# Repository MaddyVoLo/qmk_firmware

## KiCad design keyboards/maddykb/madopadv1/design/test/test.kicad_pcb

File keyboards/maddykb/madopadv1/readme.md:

# madopadv1

*A short description of the keyboard/project*

* Keyboard Maintainer: [Madeline Panak](https://github.com/VoLodiaa1)
* Hardware Supported: *The PCBs, controllers supported*
* Hardware Availability: *Links to where you can find this hardware*

Make example for this keyboard (after setting up your build environment):

    make madopadv1:default

Flashing example for this keyboard:

    make madopadv1:default:flash

See the [build environment setup](https://docs.qmk.fm/#/getting_started_build_tools) and the [make instructions](https://docs.qmk.fm/#/getting_started_make_guide) for more information. Brand new to QMK? Start with our [Complete Newbs Guide](https://docs.qmk.fm/#/newbs).

## Bootloader

Enter the bootloader in 3 ways:

* **Bootmagic reset**: Hold down the key at (0,0) in the matrix (usually the top left key or Escape) and plug in the keyboard
* **Physical reset button**: Briefly press the button on the back of the PCB - some may have pads you must short instead
* **Keycode in layout**: Press the key mapped to `QK_BOOT` if it is available

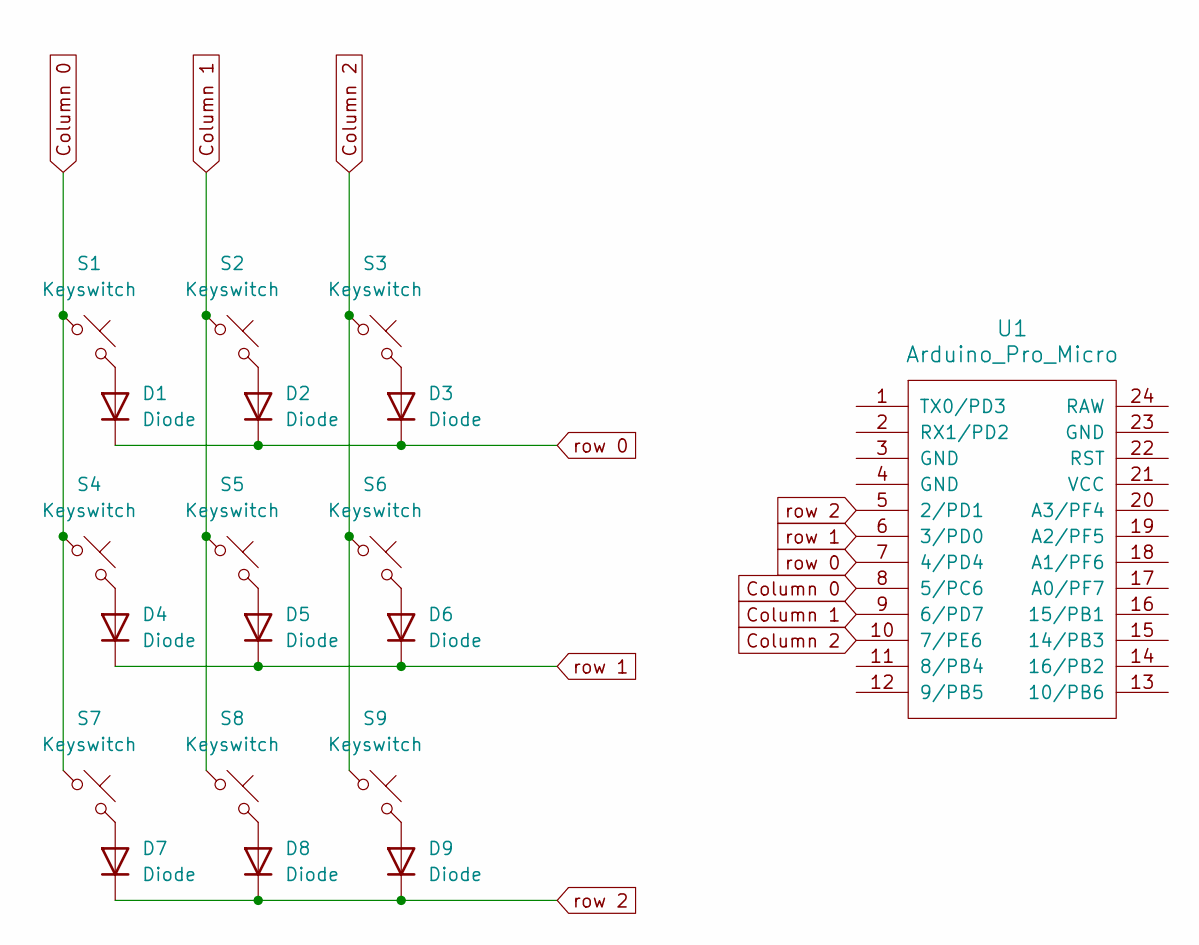
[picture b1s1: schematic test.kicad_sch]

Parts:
D1, D2, D3, D4, D5, D6, D7, D8, D9: Diode; D_SOD-123
S1, S2, S3, S4, S5, S6, S7, S8, S9: Keyswitch; MX_PCB_1.00u
U1: Arduino_Pro_Micro

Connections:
Column 0: S1.1, S4.1, S7.1, U1.8 (5/PC6)
Column 1: S2.1, S5.1, S8.1, U1.9 (6/PD7)
Column 2: S3.1, S6.1, S9.1, U1.10 (7/PE6)
unnamed: D1.2 (A), S1.2
unnamed: D2.2 (A), S2.2
unnamed: D3.2 (A), S3.2
unnamed: D4.2 (A), S4.2
unnamed: D5.2 (A), S5.2
unnamed: D6.2 (A), S6.2
unnamed: D7.2 (A), S7.2
unnamed: D8.2 (A), S8.2
unnamed: D9.2 (A), S9.2
row 0: D1.1 (K), D2.1 (K), D3.1 (K), U1.7 (4/PD4)
row 1: D4.1 (K), D5.1 (K), D6.1 (K), U1.6 (3/PD0)
row 2: D7.1 (K), D8.1 (K), D9.1 (K), U1.5 (2/PD1)

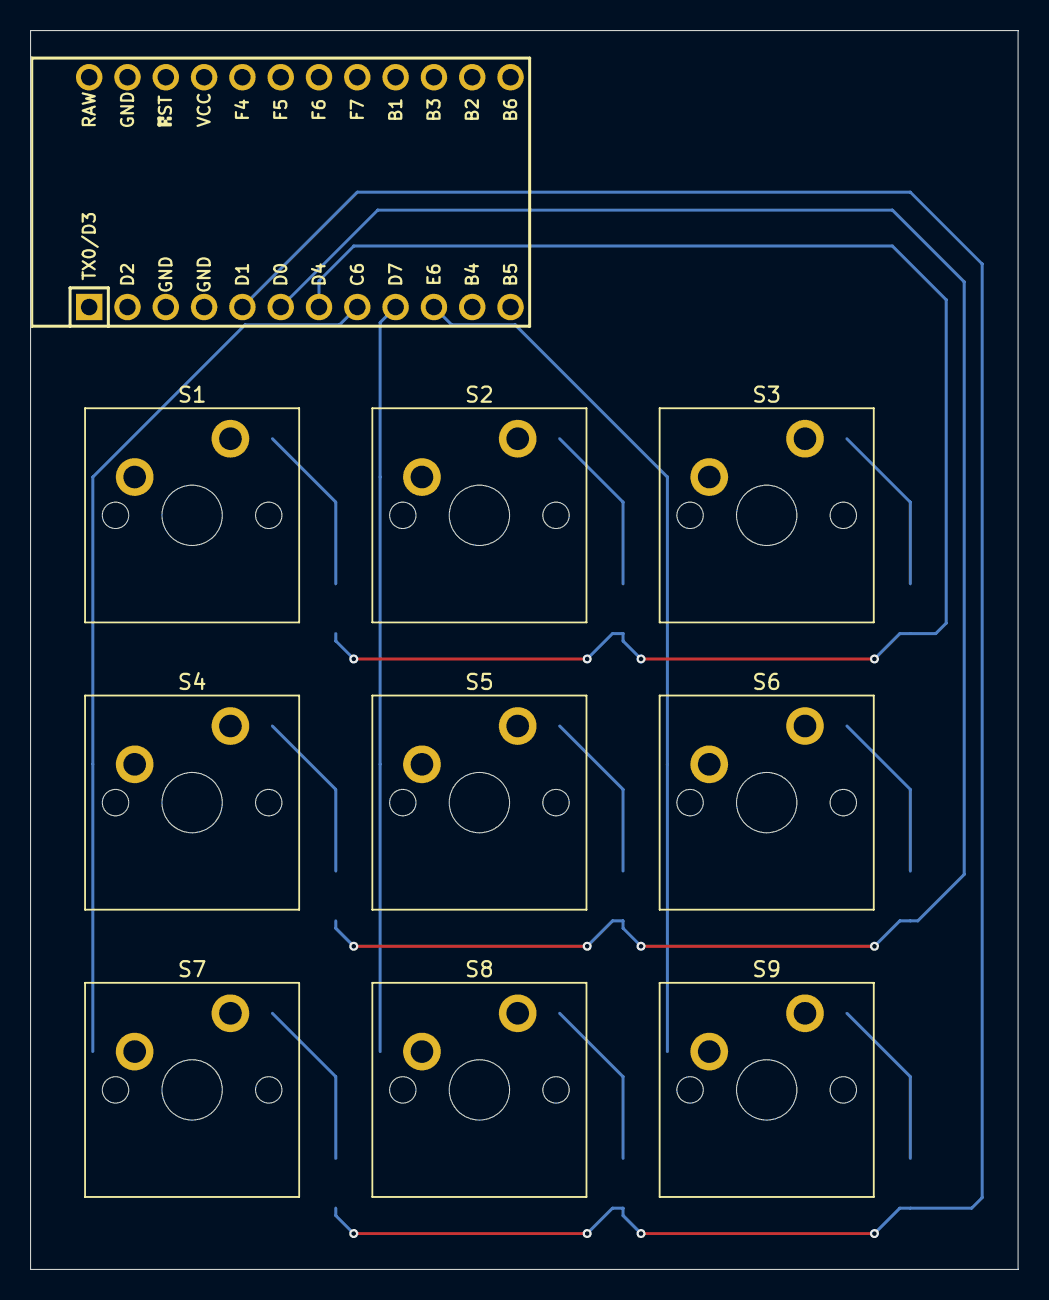
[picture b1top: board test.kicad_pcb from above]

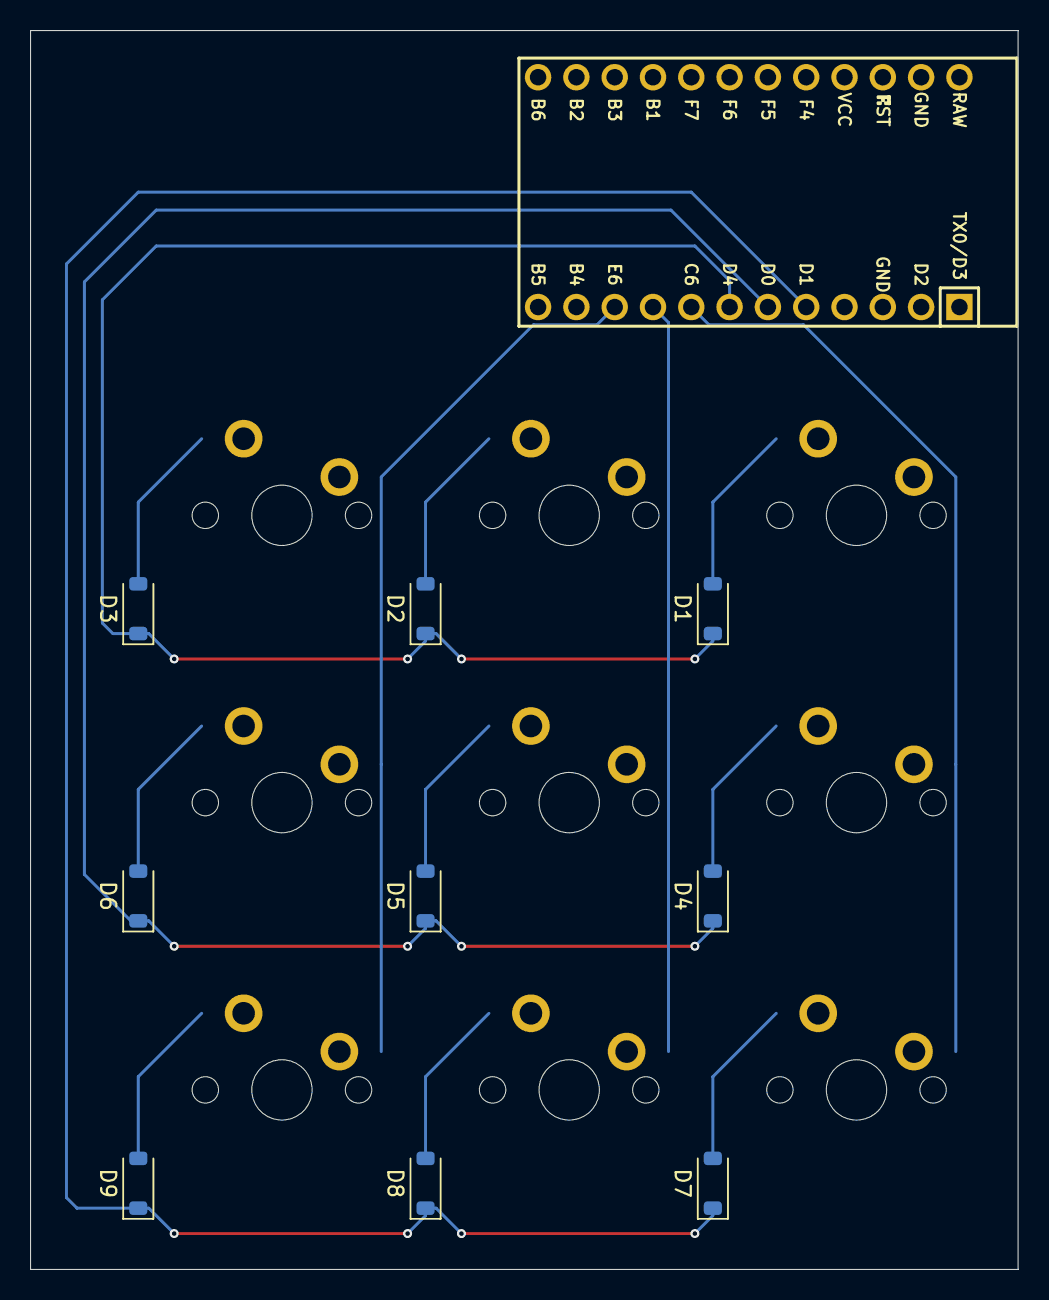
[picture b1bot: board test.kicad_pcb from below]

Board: 2 copper layers, 65.5 x 82.2 mm, 19 parts (9 on the bottom side), 15 nets.

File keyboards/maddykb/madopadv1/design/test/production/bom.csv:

Designator,Footprint,Quantity,Value,LCSC Part #
"D1, D2, D3, D4, D5, D6, D7, D8, D9",D_SOD-123,9,Diode,
"S1, S2, S3, S4, S5, S6, S7, S8, S9",Hotswap_MX_Plated_1.00u,9,Keyswitch,
U1,Arduino_Pro_Micro,1,Arduino_Pro_Micro,

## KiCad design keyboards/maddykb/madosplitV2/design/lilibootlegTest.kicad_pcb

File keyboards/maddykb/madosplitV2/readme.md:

# madosplit

*A short description of the keyboard/project*

* Keyboard Maintainer: [Madeline Panak](https://github.com/VoLodiaa1)
* Hardware Supported: *The PCBs, controllers supported*
* Hardware Availability: *Links to where you can find this hardware*

Make example for this keyboard (after setting up your build environment):

    make madosplit:default

Flashing example for this keyboard:

    make madosplit:default:flash

See the [build environment setup](https://docs.qmk.fm/#/getting_started_build_tools) and the [make instructions](https://docs.qmk.fm/#/getting_started_make_guide) for more information. Brand new to QMK? Start with our [Complete Newbs Guide](https://docs.qmk.fm/#/newbs).

## Bootloader

Enter the bootloader in 3 ways:

* **Bootmagic reset**: Hold down the key at (0,0) in the matrix (usually the top left key or Escape) and plug in the keyboard
* **Physical reset button**: Briefly press the button on the back of the PCB - some may have pads you must short instead
* **Keycode in layout**: Press the key mapped to `QK_BOOT` if it is available

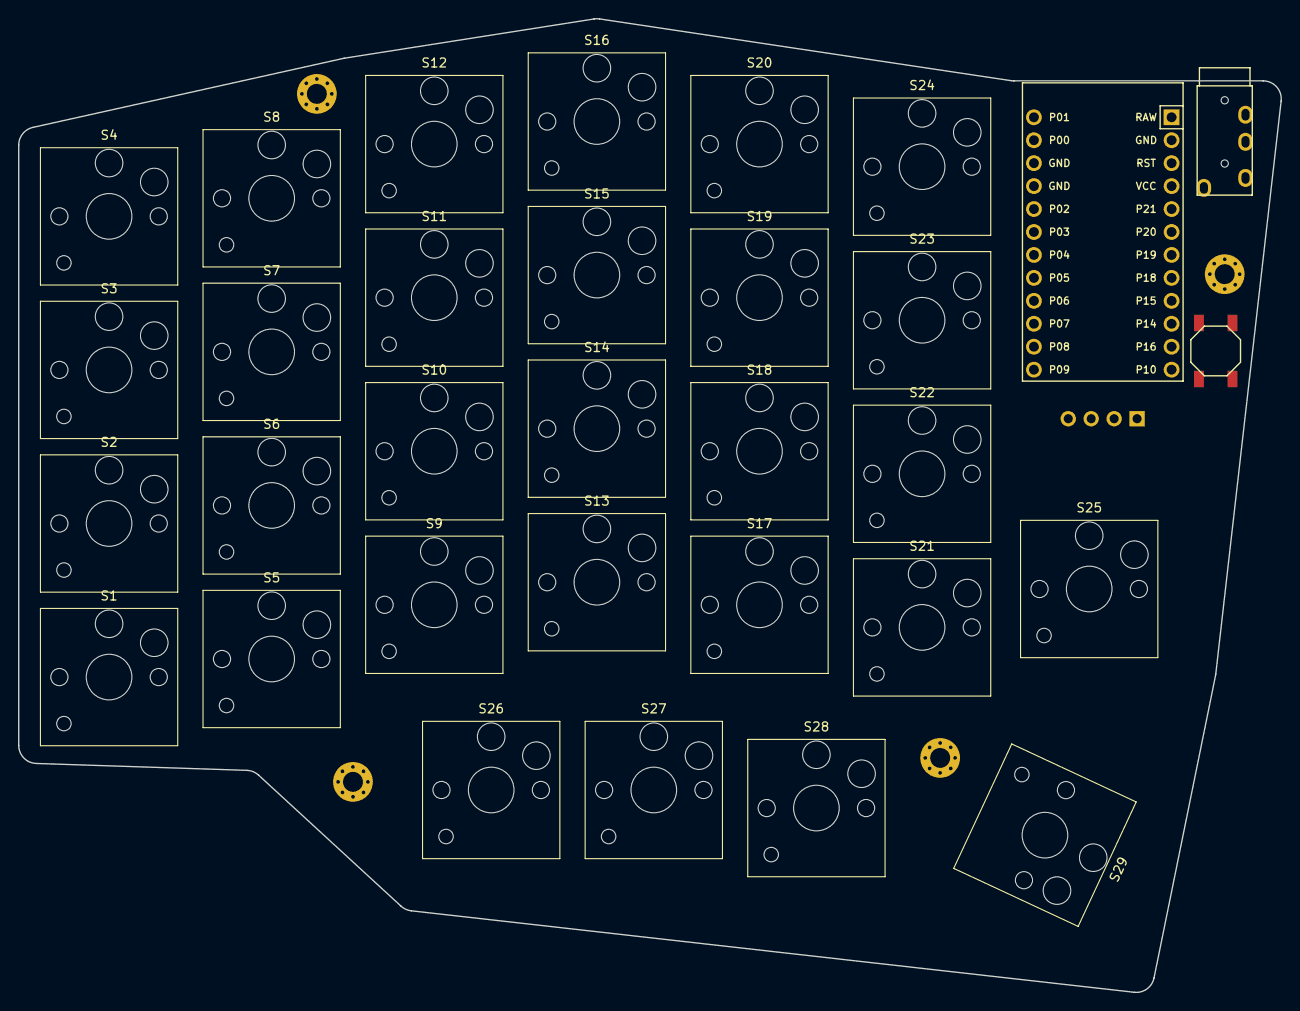
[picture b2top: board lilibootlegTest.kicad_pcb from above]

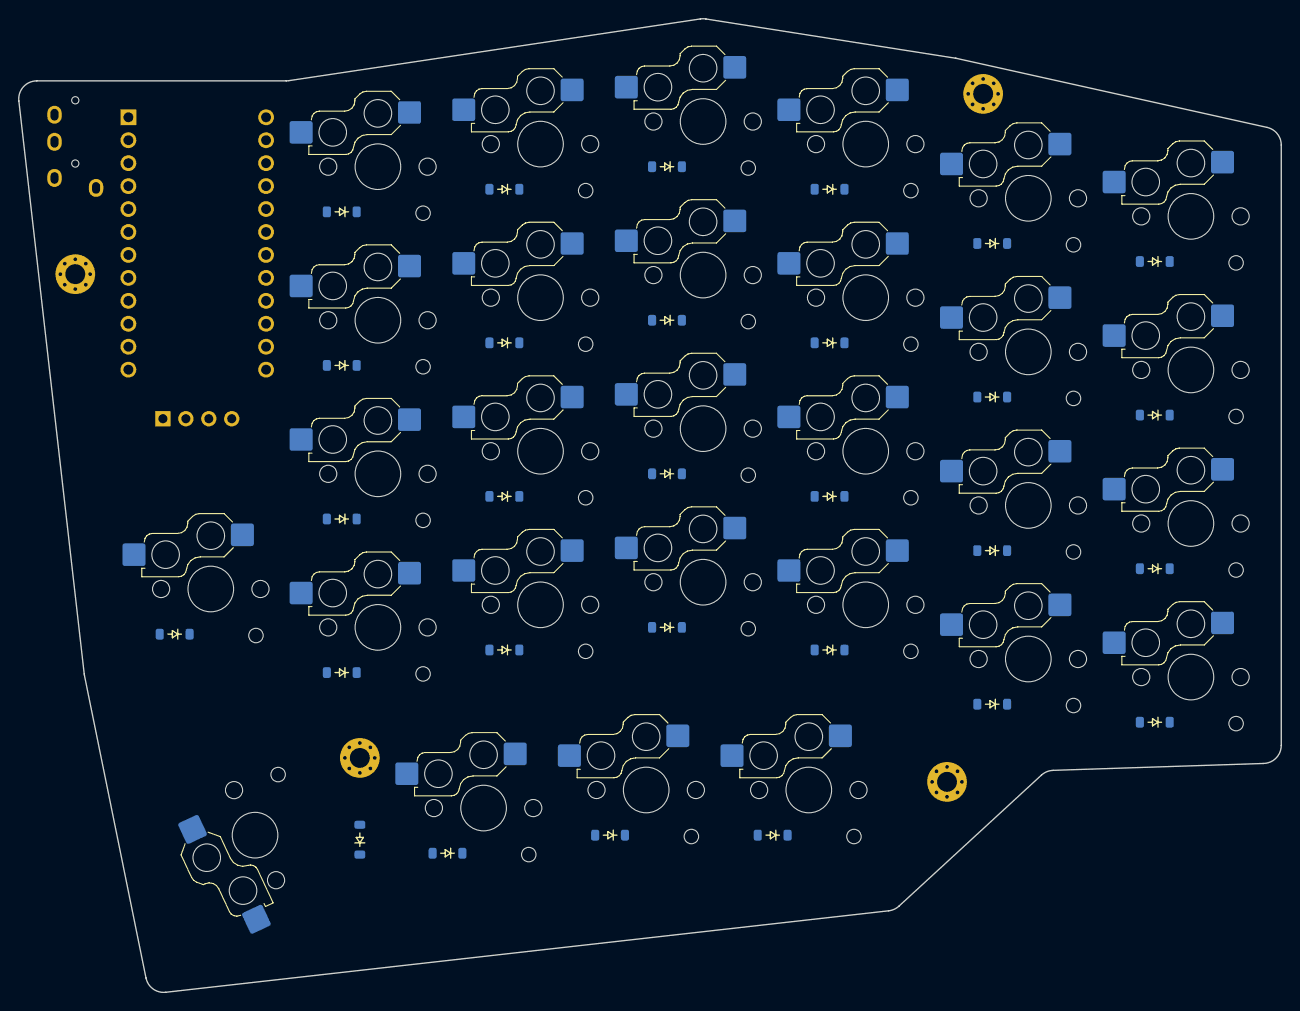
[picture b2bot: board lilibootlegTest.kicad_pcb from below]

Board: 2 copper layers, 139.8 x 107.8 mm, 66 parts (29 on the bottom side), 46 nets, no tracks yet.

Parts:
B1: SW_TACT_ALPS_SKQGABE010
D1, D2, D3, D4, D5, D6, D7, D8, D9, D10, D11, D12, D13, D14, D15, D16, D17, D18, D19, D20, D21, D22, D23, D24, D25, D26, D27, D28, D29: Diode_SOD-123
MCU1: ProMicro
OLED1: OLED; OLED_128x32
S1, S2, S3, S4, S5, S6, S7, S8, S9, S10, S11, S12, S13, S14, S15, S16, S17, S18, S19, S20, S21, S22, S23, S24, S25, S26, S27, S28: Hotswap_Choc_V1V2_1.00u
S29: Hotswap_Choc_V1V2_1.50u
TRRS1: TRRS_PJ-320A
_1, _2, _3, _4: MountingHole_2.2mm_M2_Pad_Via

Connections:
GND: B1.2, MCU1.2, MCU1.15, MCU1.16, OLED1.1, TRRS1.1, TRRS1.2
P0: MCU1.14, TRRS1.3
P2: MCU1.17, OLED1.3
P3: MCU1.18, OLED1.4
P5: D4.1, D8.1, D12.1, D16.1, D20.1, D24.1, MCU1.20
P6: D3.1, D7.1, D11.1, D15.1, D19.1, D23.1, MCU1.21
P7: D2.1, D6.1, D10.1, D14.1, D18.1, D22.1, MCU1.22
P8: D1.1, D5.1, D9.1, D13.1, D17.1, D21.1, MCU1.23
P9: D25.1, D26.1, D27.1, D28.1, D29.1, MCU1.24
P10: MCU1.12, S21.1, S22.1, S23.1, S24.1, S25.1, S29.1
P14: MCU1.10, S13.1, S14.1, S15.1, S16.1, S27.1
P15: MCU1.9, S9.1, S10.1, S11.1, S12.1, S26.1
P16: MCU1.11, S17.1, S18.1, S19.1, S20.1, S28.1
P18: MCU1.8, S5.1, S6.1, S7.1, S8.1
P19: MCU1.7, S1.1, S2.1, S3.1, S4.1
RST: B1.1, MCU1.3
VCC: MCU1.4, OLED1.2, TRRS1.4
index_bot: D17.2, S17.2
index_mid: D18.2, S18.2
index_num: D20.2, S20.2
index_top: D19.2, S19.2
inner_bot: D21.2, S21.2
inner_mid: D22.2, S22.2
inner_num: D24.2, S24.2
inner_top: D23.2, S23.2
middle_bot: D13.2, S13.2
middle_mid: D14.2, S14.2
middle_num: D16.2, S16.2
middle_top: D15.2, S15.2
mod_bot: D1.2, S1.2
mod_mid: D2.2, S2.2
mod_num: D4.2, S4.2
mod_top: D3.2, S3.2
pinky_bot: D5.2, S5.2
pinky_mid: D6.2, S6.2
pinky_num: D8.2, S8.2
pinky_top: D7.2, S7.2
reach_reach: D25.2, S25.2
reachy_stretch: D29.2, S29.2
ring_bot: D9.2, S9.2
ring_mid: D10.2, S10.2
ring_num: D12.2, S12.2
ring_top: D11.2, S11.2
tucky1_stretch: D26.2, S26.2
tucky2_stretch: D27.2, S27.2
tucky3_stretch: D28.2, S28.2

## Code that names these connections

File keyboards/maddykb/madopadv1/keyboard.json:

{
    "manufacturer": "Madeline Panak",
    "keyboard_name": "madopadv1",
    "maintainer": "VoLodiaa1",
    "bootloader": "atmel-dfu",
    "diode_direction": "COL2ROW",
    "features": {
        "bootmagic": true,
        "command": false,
        "console": false,
        "extrakey": true,
        "mousekey": true,
        "nkro": true
    },
    "matrix_pins": {
        "cols": ["PC6", "PD7", "PE6"],
        "rows": ["PD4", "PD0", "PD1"]
    },
    "processor": "atmega32u4",
    "url": "",
    "usb": {
        "device_version": "1.0.0",
        "pid": "0x0000",
        "vid": "0xFEED"
    },
    "layouts": {
        "LAYOUT_numpad_3x3": {
            "layout": [
                {"matrix": [0, 0], "x": 0, "y": 0},
                {"matrix": [0, 1], "x": 1, "y": 0},
                {"matrix": [0, 2], "x": 2, "y": 0},
                {"matrix": [1, 0], "x": 0, "y": 1},
                {"matrix": [1, 1], "x": 1, "y": 1},
                {"matrix": [1, 2], "x": 2, "y": 1},
                {"matrix": [2, 0], "x": 0, "y": 2},
                {"matrix": [2, 1], "x": 1, "y": 2},
                {"matrix": [2, 2], "x": 2, "y": 2},
                {"matrix": [3, 0], "x": 0, "y": 3},
                {"matrix": [3, 1], "x": 1, "y": 3},
                {"matrix": [3, 2], "x": 2, "y": 3}
            ]
        }
    }
}

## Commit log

2024-08-28 Added maddykb to repo
2024-08-28 done wiring both board, missing resistors
2024-09-07 MadoSplit PCB finish
2024-09-08 Bottom case and production files
2024-09-16 Keymapping done
2024-10-15 Debugged Firmware Case + gasket STL
2024-11-25 fixed the qwerty to colemak shortcut
2025-08-12 Started madosplitV2 and fixed some layout issues on V1
